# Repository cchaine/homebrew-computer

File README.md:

# Homebrew Computer

Design documents and details about my microprocessorless computer.

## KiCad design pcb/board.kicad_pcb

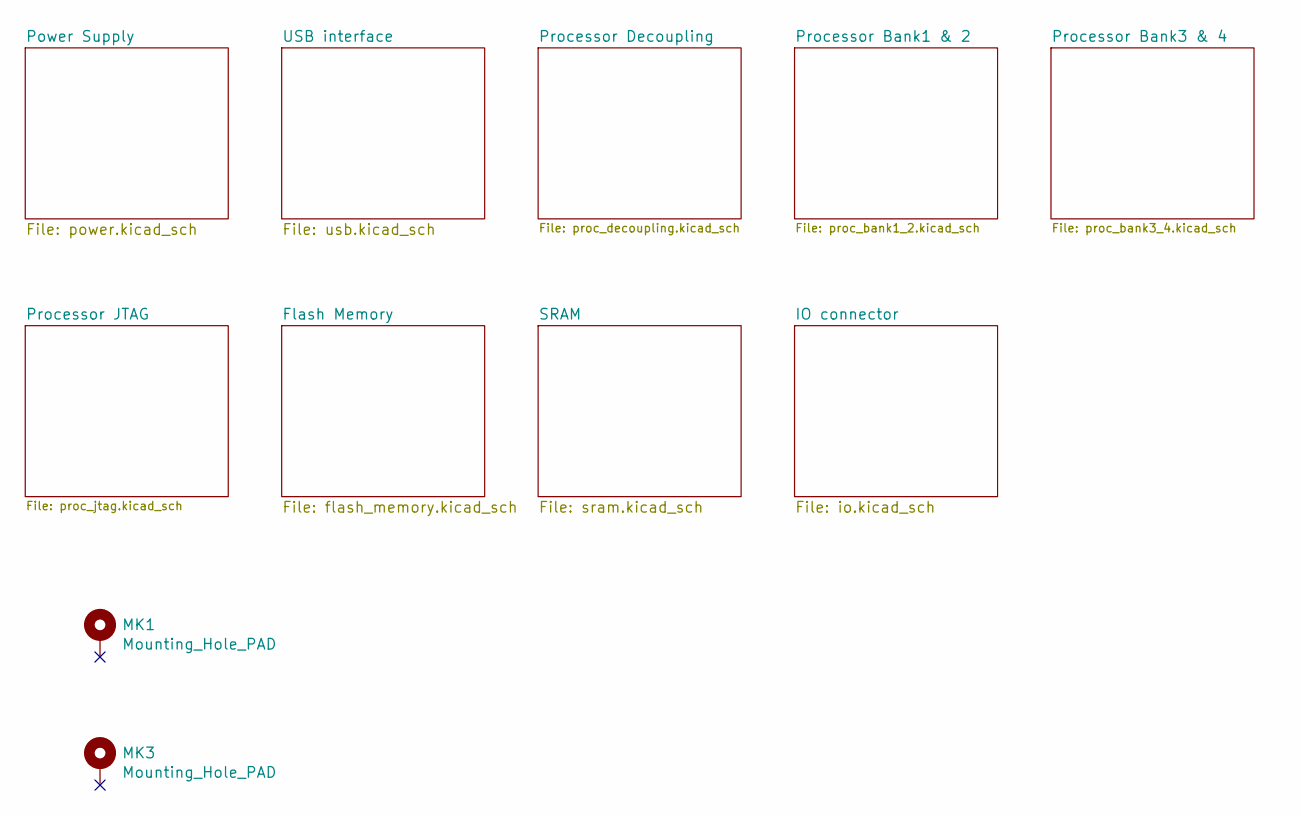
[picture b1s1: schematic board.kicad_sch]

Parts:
MK1, MK3: Mounting_Hole_PAD; MountingHole_2.7mm

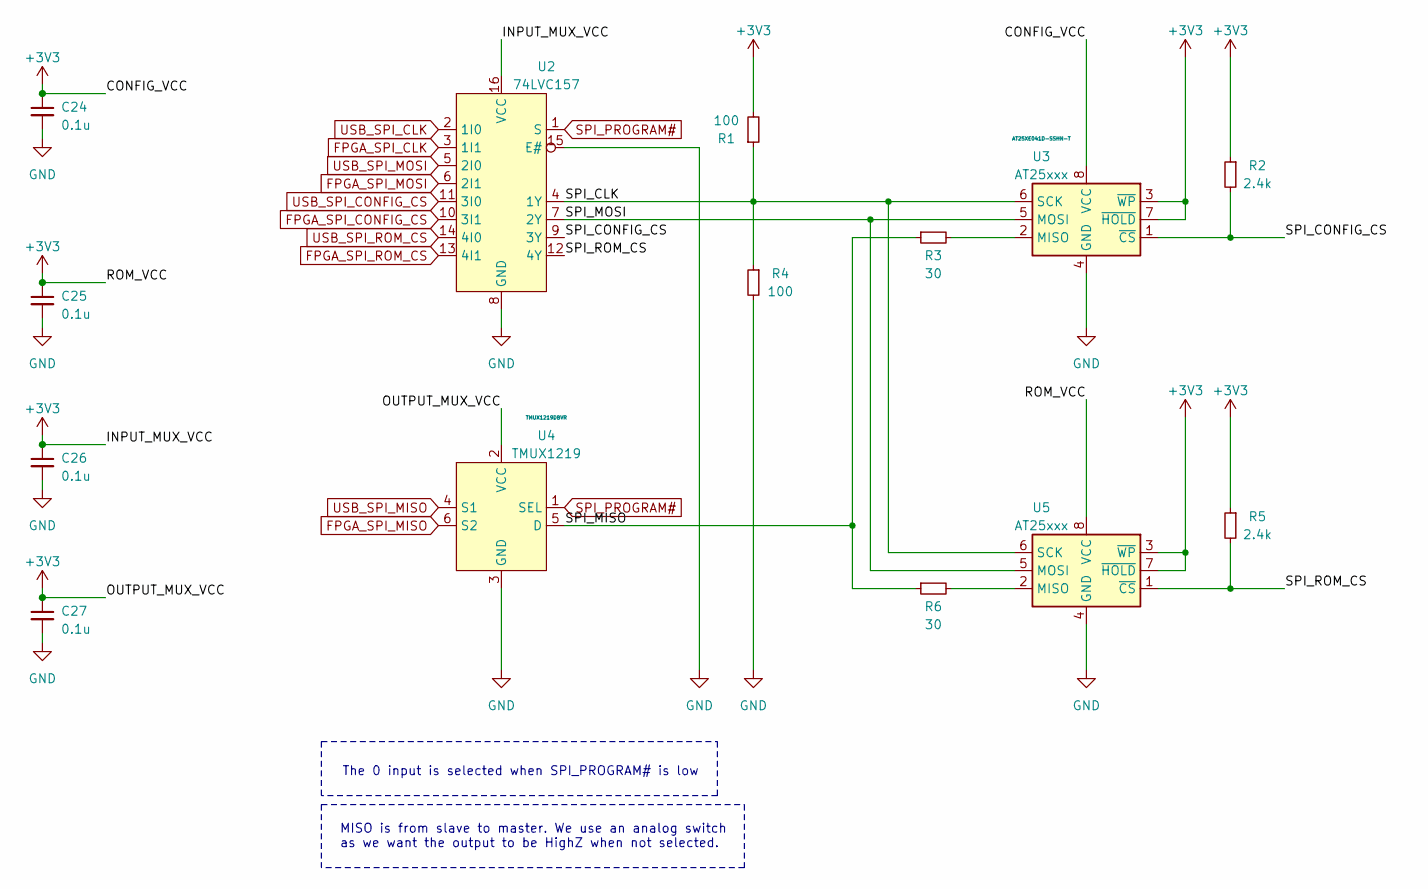
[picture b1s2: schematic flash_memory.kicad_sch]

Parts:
C24, C25, C26, C27: 0.1u; C_0402_1005Metric
R1, R4: 100; R_0402_1005Metric
R2, R5: 2.4k; R_0402_1005Metric
R3, R6: 30; R_0402_1005Metric
U2: 74LVC157; TSSOP-16_4.4x5mm_P0.65mm
U3, U5: AT25xxx; SOIC-8_3.9x4.9mm_P1.27mm
U4: TMUX1219; SOT-23-6

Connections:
/Flash Memory/SPI_CLK: R1.1, R4.1, U2.4 (1Y), U3.6 (SCK), U5.6 (SCK)
/Flash Memory/SPI_CONFIG_CS: R2.2, U2.9 (3Y), U3.1 (~CS)
/Flash Memory/SPI_MISO: R3.1, R6.1, U4.5 (D)
/Flash Memory/SPI_MOSI: U2.7 (2Y), U3.5 (MOSI), U5.5 (MOSI)
/Flash Memory/SPI_ROM_CS: R5.2, U2.12 (4Y), U5.1 (~CS)
FPGA_SPI_CLK: U2.3 (1I1); also elsewhere on the board
FPGA_SPI_CONFIG_CS: U2.10 (3I1); also elsewhere on the board
FPGA_SPI_MISO: U4.6 (S2); also elsewhere on the board
FPGA_SPI_MOSI: U2.6 (2I1); also elsewhere on the board
FPGA_SPI_ROM_CS: U2.13 (4I1); also elsewhere on the board
GND: C24.2, C25.2, C26.2, C27.2, R4.2, U2.8 (GND), U2.15 (E#), U3.4 (GND), U4.3 (GND), U5.4 (GND); also elsewhere on the board
unnamed: R3.2, U3.2 (MISO)
unnamed: R6.2, U5.2 (MISO)
SPI_PROGRAM#: U2.1 (S), U4.1 (SEL); also elsewhere on the board
USB_SPI_CLK: U2.2 (1I0); also elsewhere on the board
USB_SPI_CONFIG_CS: U2.11 (3I0); also elsewhere on the board
USB_SPI_MISO: U4.4 (S1); also elsewhere on the board
USB_SPI_MOSI: U2.5 (2I0); also elsewhere on the board
USB_SPI_ROM_CS: U2.14 (4I0); also elsewhere on the board
VCCAUX: C24.1, C25.1, C26.1, C27.1, R1.2, R2.1, R5.1, U2.16 (VCC), U3.3 (~WP), U3.7 (~HOLD), U3.8 (VCC), U4.2 (VCC), U5.3 (~WP), U5.7 (~HOLD), U5.8 (VCC); also elsewhere on the board

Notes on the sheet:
MISO is from slave to master. We use an analog switch as we want the output to be HighZ when not selected.
The 0 input is selected when SPI_PROGRAM# is low

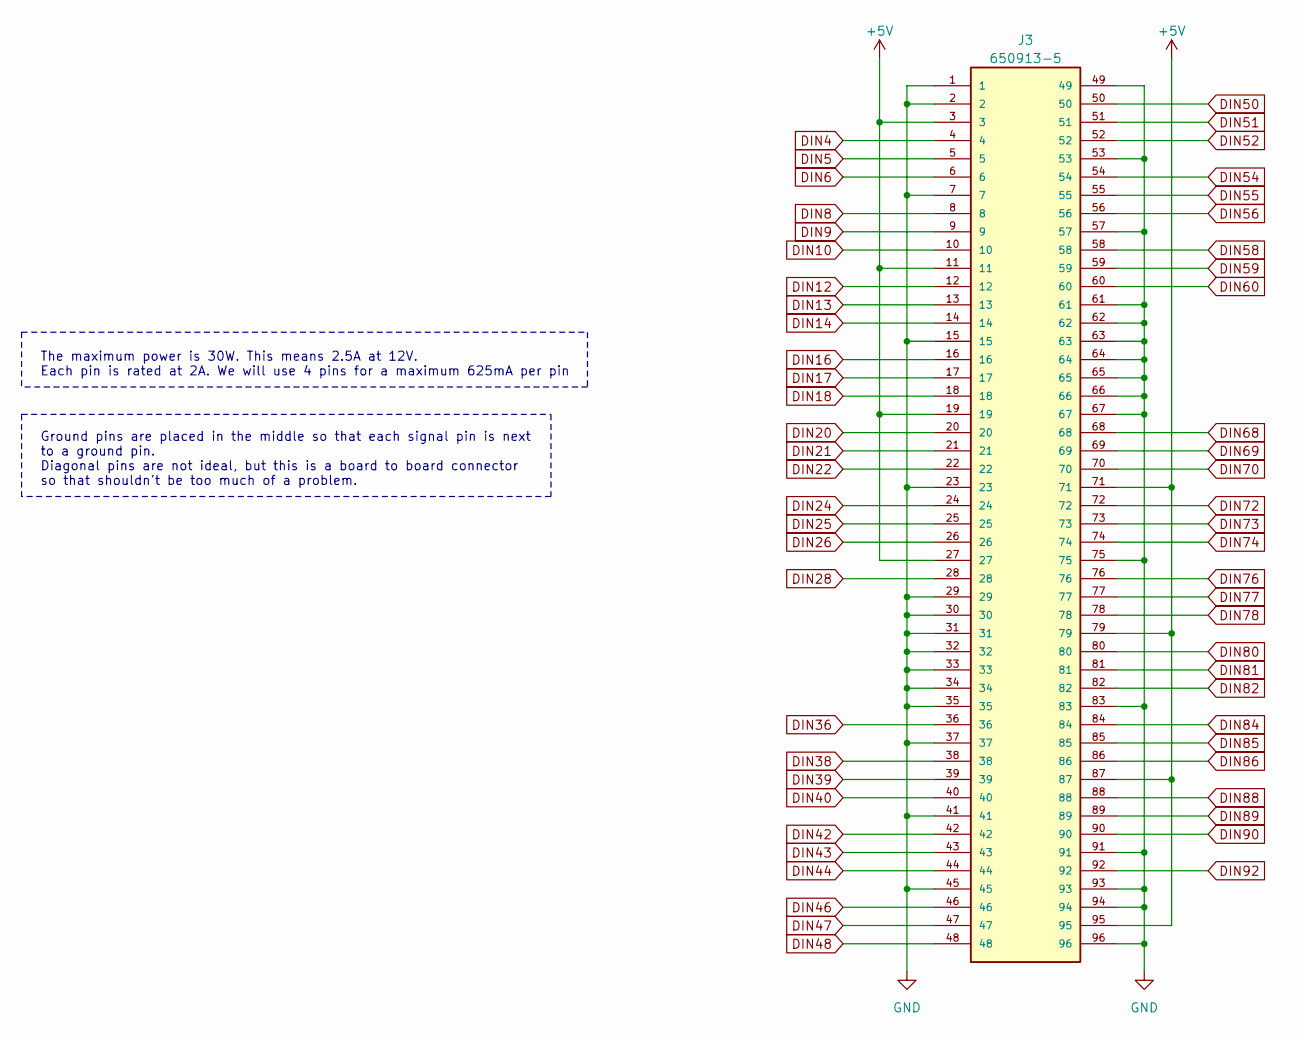
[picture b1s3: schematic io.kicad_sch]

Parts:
J3: 650913-5; TE_650913-5

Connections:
+5V: J3.3, J3.11, J3.19, J3.27, J3.71, J3.79, J3.87, J3.95; also elsewhere on the board
DIN4: J3.4; also elsewhere on the board
DIN5: J3.5; also elsewhere on the board
DIN6: J3.6; also elsewhere on the board
DIN8: J3.8; also elsewhere on the board
DIN9: J3.9; also elsewhere on the board
DIN10: J3.10; also elsewhere on the board
DIN12: J3.12; also elsewhere on the board
DIN13: J3.13; also elsewhere on the board
DIN14: J3.14; also elsewhere on the board
DIN16: J3.16; also elsewhere on the board
DIN17: J3.17; also elsewhere on the board
DIN18: J3.18; also elsewhere on the board
DIN20: J3.20; also elsewhere on the board
DIN21: J3.21; also elsewhere on the board
DIN22: J3.22; also elsewhere on the board
DIN24: J3.24; also elsewhere on the board
DIN25: J3.25; also elsewhere on the board
DIN26: J3.26; also elsewhere on the board
DIN28: J3.28; also elsewhere on the board
DIN36: J3.36; also elsewhere on the board
DIN38: J3.38; also elsewhere on the board
DIN39: J3.39; also elsewhere on the board
DIN40: J3.40; also elsewhere on the board
DIN42: J3.42; also elsewhere on the board
DIN43: J3.43; also elsewhere on the board
DIN44: J3.44; also elsewhere on the board
DIN46: J3.46; also elsewhere on the board
DIN47: J3.47; also elsewhere on the board
DIN48: J3.48; also elsewhere on the board
DIN50: J3.50; also elsewhere on the board
DIN51: J3.51; also elsewhere on the board
DIN52: J3.52; also elsewhere on the board
DIN54: J3.54; also elsewhere on the board
DIN55: J3.55; also elsewhere on the board
DIN56: J3.56; also elsewhere on the board
DIN58: J3.58; also elsewhere on the board
DIN59: J3.59; also elsewhere on the board
DIN60: J3.60; also elsewhere on the board
DIN68: J3.68; also elsewhere on the board
DIN69: J3.69; also elsewhere on the board
DIN70: J3.70; also elsewhere on the board
DIN72: J3.72; also elsewhere on the board
DIN73: J3.73; also elsewhere on the board
DIN74: J3.74; also elsewhere on the board
DIN76: J3.76; also elsewhere on the board
DIN77: J3.77; also elsewhere on the board
DIN78: J3.78; also elsewhere on the board
DIN80: J3.80; also elsewhere on the board
DIN81: J3.81; also elsewhere on the board
DIN82: J3.82; also elsewhere on the board
DIN84: J3.84; also elsewhere on the board
DIN85: J3.85; also elsewhere on the board
DIN86: J3.86; also elsewhere on the board
DIN88: J3.88; also elsewhere on the board
DIN89: J3.89; also elsewhere on the board
DIN90: J3.90; also elsewhere on the board
DIN92: J3.92; also elsewhere on the board
GND: J3.1, J3.2, J3.7, J3.15, J3.23, J3.29, J3.30, J3.31, J3.32, J3.33, J3.34, J3.35, J3.37, J3.41, J3.45, J3.49, J3.53, J3.57, J3.61, J3.62, J3.63, J3.64, J3.65, J3.66, J3.67, J3.75, J3.83, J3.91, J3.93, J3.94, J3.96; also elsewhere on the board

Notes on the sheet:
The maximum power is 30W. This means 2.5A at 12V. Each pin is rated at 2A. We will use 4 pins for a maximum 625mA per pin
Ground pins are placed in the middle so that each signal pin is next to a ground pin. Diagonal pins are not ideal, but this is a board to board connector so that shouldn't be too much of a problem.

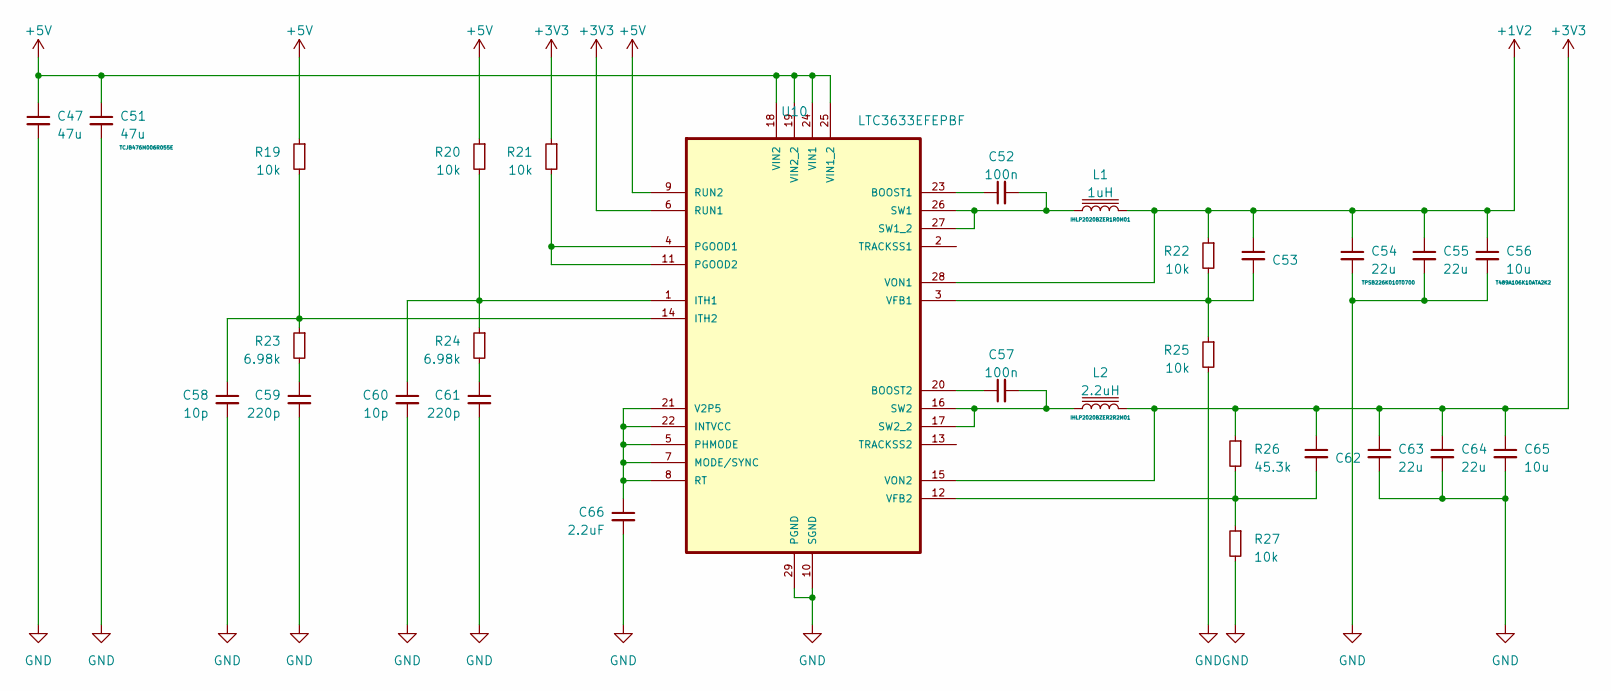
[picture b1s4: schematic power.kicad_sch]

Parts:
C47, C51: 47u; C_1210_3225Metric
C52, C57: 100n; C_0402_1005Metric
C53, C62: NL; C_0603_1608Metric
C54, C55, C63, C64: 22u; C_1206_3216Metric
C56, C65: 10u; C_1206_3216Metric
C58, C60: 10p; C_0402_1005Metric
C59, C61: 220p; C_0402_1005Metric
C66: 2.2uF; C_0603_1608Metric
L1: 1uH; IND_#A915BY-100M=P3
L2: 2.2uH; IND_#A915BY-100M=P3
R19, R20, R21, R22, R25, R27: 10k; R_0402_1005Metric
R23, R24: 6.98k; R_0402_1005Metric
R26: 45.3k; R_0402_1005Metric
U10: LTC3633EFEPBF; SOP65P640X120-29N

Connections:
+5V: C47.1, C51.1, R19.1, R20.1, U10.9 (RUN2), U10.18 (VIN2), U10.19 (VIN2_2), U10.24 (VIN1), U10.25 (VIN1_2); also elsewhere on the board
GND: C47.2, C51.2, C54.2, C55.2, C56.2, C58.2, C59.2, C60.2, C61.2, C63.2, C64.2, C65.2, C66.2, R25.2, R27.2, U10.10 (SGND), U10.29 (PGND); also elsewhere on the board
unnamed: C52.1, U10.23 (BOOST1)
unnamed: C52.2, L1.1, U10.26 (SW1), U10.27 (SW1_2)
unnamed: C53.2, R22.2, R25.1, U10.3 (VFB1)
unnamed: C57.1, U10.20 (BOOST2)
unnamed: C57.2, L2.1, U10.16 (SW2), U10.17 (SW2_2)
unnamed: C58.1, R19.2, R23.1, U10.14 (ITH2)
unnamed: C59.1, R23.2
unnamed: C60.1, R20.2, R24.1, U10.1 (ITH1)
unnamed: C61.1, R24.2
unnamed: C62.2, R26.2, R27.1, U10.12 (VFB2)
unnamed: C66.1, U10.5 (PHMODE), U10.7 (MODE/SYNC), U10.8 (RT), U10.21 (V2P5), U10.22 (INTVCC)
unnamed: R21.2, U10.4 (PGOOD1), U10.11 (PGOOD2)
VCCAUX: C62.1, C63.1, C64.1, C65.1, L2.2, R21.1, R26.1, U10.6 (RUN1), U10.15 (VON2); also elsewhere on the board
VCCINT: C53.1, C54.1, C55.1, C56.1, L1.2, R22.1, U10.28 (VON1); also elsewhere on the board

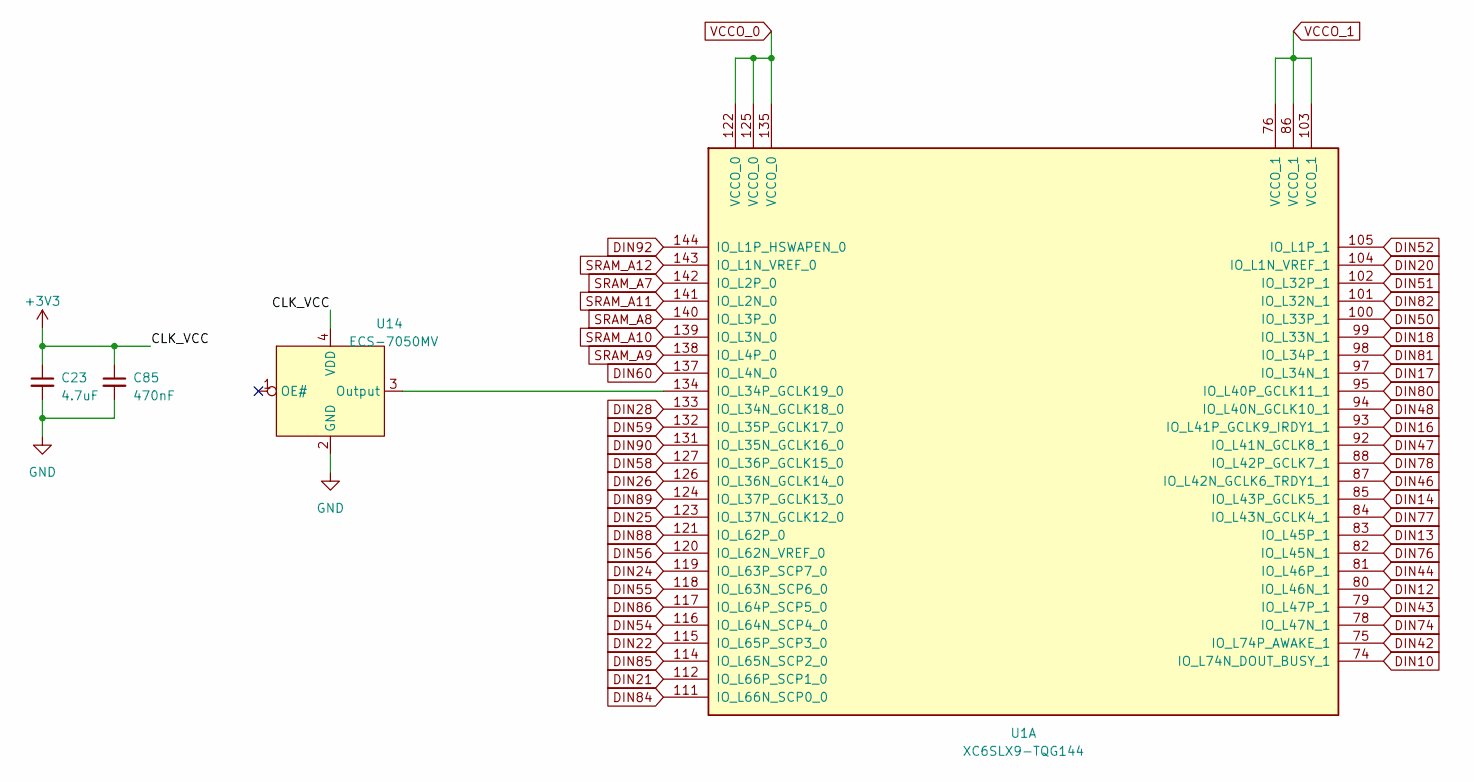
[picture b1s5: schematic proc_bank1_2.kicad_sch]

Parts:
C23: 4.7uF; C_0805_2012Metric
C85: 470nF; C_0402_1005Metric
U1: XC6SLX9-TQG144; TQFP-144_20x20mm_P0.5mm
U14: ECS-7050MV

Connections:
DIN10: U1.74 (IO_L74N_DOUT_BUSY_1); also elsewhere on the board
DIN12: U1.80 (IO_L46N_1); also elsewhere on the board
DIN13: U1.83 (IO_L45P_1); also elsewhere on the board
DIN14: U1.85 (IO_L43P_GCLK5_1); also elsewhere on the board
DIN16: U1.93 (IO_L41P_GCLK9_IRDY1_1); also elsewhere on the board
DIN17: U1.97 (IO_L34N_1); also elsewhere on the board
DIN18: U1.99 (IO_L33N_1); also elsewhere on the board
DIN20: U1.104 (IO_L1N_VREF_1); also elsewhere on the board
DIN21: U1.112 (IO_L66P_SCP1_0); also elsewhere on the board
DIN22: U1.115 (IO_L65P_SCP3_0); also elsewhere on the board
DIN24: U1.119 (IO_L63P_SCP7_0); also elsewhere on the board
DIN25: U1.123 (IO_L37N_GCLK12_0); also elsewhere on the board
DIN26: U1.126 (IO_L36N_GCLK14_0); also elsewhere on the board
DIN28: U1.133 (IO_L34N_GCLK18_0); also elsewhere on the board
DIN42: U1.75 (IO_L74P_AWAKE_1); also elsewhere on the board
DIN43: U1.79 (IO_L47P_1); also elsewhere on the board
DIN44: U1.81 (IO_L46P_1); also elsewhere on the board
DIN46: U1.87 (IO_L42N_GCLK6_TRDY1_1); also elsewhere on the board
DIN47: U1.92 (IO_L41N_GCLK8_1); also elsewhere on the board
DIN48: U1.94 (IO_L40N_GCLK10_1); also elsewhere on the board
DIN50: U1.100 (IO_L33P_1); also elsewhere on the board
DIN51: U1.102 (IO_L32P_1); also elsewhere on the board
DIN52: U1.105 (IO_L1P_1); also elsewhere on the board
DIN54: U1.116 (IO_L64N_SCP4_0); also elsewhere on the board
DIN55: U1.118 (IO_L63N_SCP6_0); also elsewhere on the board
DIN56: U1.120 (IO_L62N_VREF_0); also elsewhere on the board
DIN58: U1.127 (IO_L36P_GCLK15_0); also elsewhere on the board
DIN59: U1.132 (IO_L35P_GCLK17_0); also elsewhere on the board
DIN60: U1.137 (IO_L4N_0); also elsewhere on the board
DIN74: U1.78 (IO_L47N_1); also elsewhere on the board
DIN76: U1.82 (IO_L45N_1); also elsewhere on the board
DIN77: U1.84 (IO_L43N_GCLK4_1); also elsewhere on the board
DIN78: U1.88 (IO_L42P_GCLK7_1); also elsewhere on the board
DIN80: U1.95 (IO_L40P_GCLK11_1); also elsewhere on the board
DIN81: U1.98 (IO_L34P_1); also elsewhere on the board
DIN82: U1.101 (IO_L32N_1); also elsewhere on the board
DIN84: U1.111 (IO_L66N_SCP0_0); also elsewhere on the board
DIN85: U1.114 (IO_L65N_SCP2_0); also elsewhere on the board
DIN86: U1.117 (IO_L64P_SCP5_0); also elsewhere on the board
DIN88: U1.121 (IO_L62P_0); also elsewhere on the board
DIN89: U1.124 (IO_L37P_GCLK13_0); also elsewhere on the board
DIN90: U1.131 (IO_L35N_GCLK16_0); also elsewhere on the board
DIN92: U1.144 (IO_L1P_HSWAPEN_0); also elsewhere on the board
GND: C23.2, C85.2, U14.2 (GND); also elsewhere on the board
unnamed: U1.134 (IO_L34P_GCLK19_0), U14.3 (Output)
SRAM_A7: U1.142 (IO_L2P_0); also elsewhere on the board
SRAM_A8: U1.140 (IO_L3P_0); also elsewhere on the board
SRAM_A9: U1.138 (IO_L4P_0); also elsewhere on the board
SRAM_A10: U1.139 (IO_L3N_0); also elsewhere on the board
SRAM_A11: U1.141 (IO_L2N_0); also elsewhere on the board
SRAM_A12: U1.143 (IO_L1N_VREF_0); also elsewhere on the board
VCCAUX: C23.1, C85.1, U1.76 (VCCO_1), U1.86 (VCCO_1), U1.103 (VCCO_1), U1.122 (VCCO_0), U1.125 (VCCO_0), U1.135 (VCCO_0), U14.4 (VDD); also elsewhere on the board

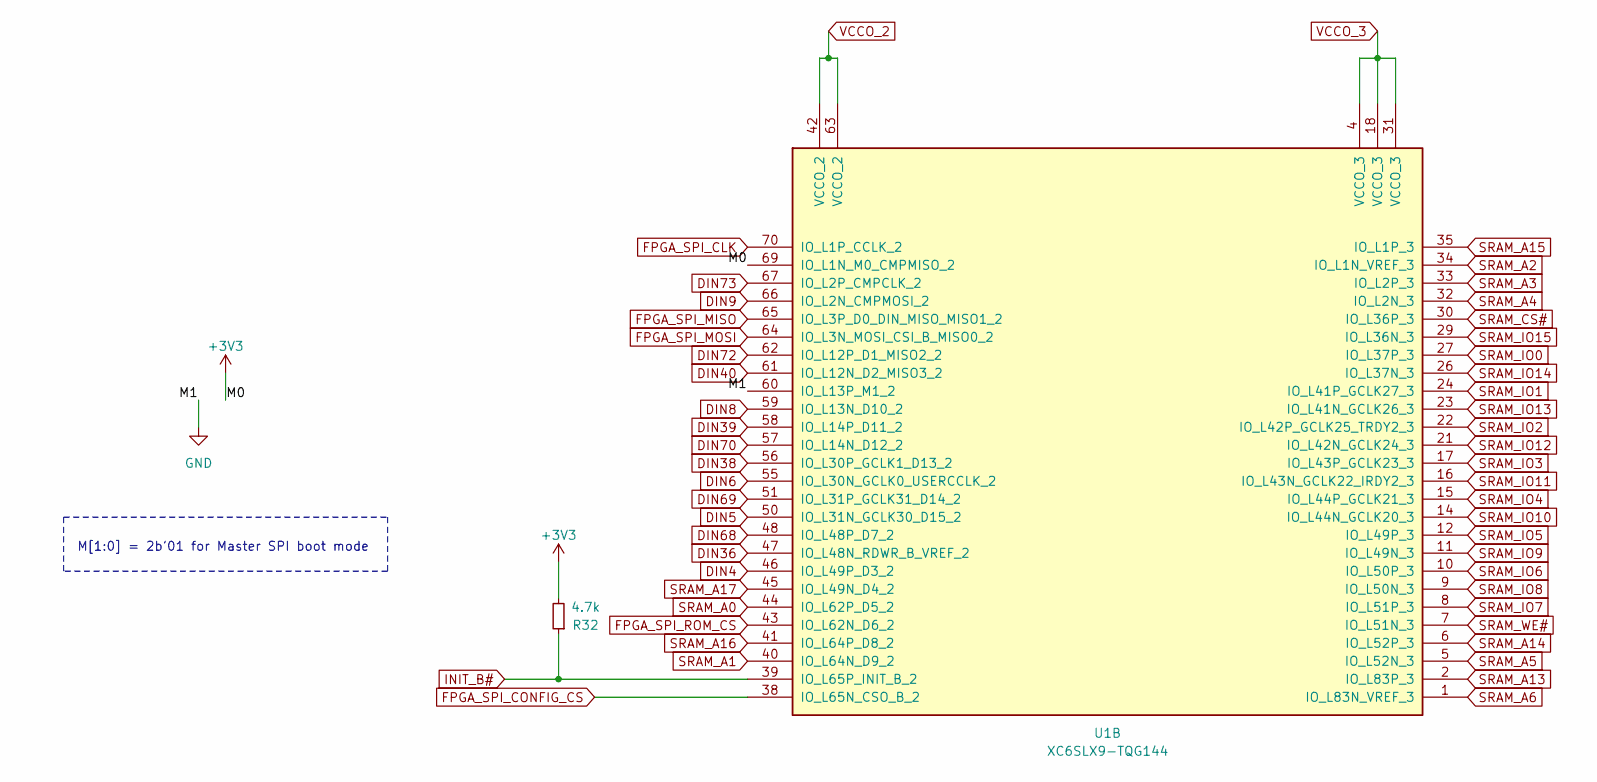
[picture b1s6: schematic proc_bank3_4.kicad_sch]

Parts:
R32: 4.7k; R_0402_1005Metric
U1: XC6SLX9-TQG144; TQFP-144_20x20mm_P0.5mm

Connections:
DIN4: U1.46 (IO_L49P_D3_2); also elsewhere on the board
DIN5: U1.50 (IO_L31N_GCLK30_D15_2); also elsewhere on the board
DIN6: U1.55 (IO_L30N_GCLK0_USERCCLK_2); also elsewhere on the board
DIN8: U1.59 (IO_L13N_D10_2); also elsewhere on the board
DIN9: U1.66 (IO_L2N_CMPMOSI_2); also elsewhere on the board
DIN36: U1.47 (IO_L48N_RDWR_B_VREF_2); also elsewhere on the board
DIN38: U1.56 (IO_L30P_GCLK1_D13_2); also elsewhere on the board
DIN39: U1.58 (IO_L14P_D11_2); also elsewhere on the board
DIN40: U1.61 (IO_L12N_D2_MISO3_2); also elsewhere on the board
DIN68: U1.48 (IO_L48P_D7_2); also elsewhere on the board
DIN69: U1.51 (IO_L31P_GCLK31_D14_2); also elsewhere on the board
DIN70: U1.57 (IO_L14N_D12_2); also elsewhere on the board
DIN72: U1.62 (IO_L12P_D1_MISO2_2); also elsewhere on the board
DIN73: U1.67 (IO_L2P_CMPCLK_2); also elsewhere on the board
FPGA_SPI_CLK: U1.70 (IO_L1P_CCLK_2); also elsewhere on the board
FPGA_SPI_CONFIG_CS: U1.38 (IO_L65N_CSO_B_2); also elsewhere on the board
FPGA_SPI_MISO: U1.65 (IO_L3P_D0_DIN_MISO_MISO1_2); also elsewhere on the board
FPGA_SPI_MOSI: U1.64 (IO_L3N_MOSI_CSI_B_MISO0_2); also elsewhere on the board
FPGA_SPI_ROM_CS: U1.43 (IO_L62N_D6_2); also elsewhere on the board
GND: U1.60 (IO_L13P_M1_2); also elsewhere on the board
INIT_B#: R32.1, U1.39 (IO_L65P_INIT_B_2); also elsewhere on the board
SRAM_A0: U1.44 (IO_L62P_D5_2); also elsewhere on the board
SRAM_A1: U1.40 (IO_L64N_D9_2); also elsewhere on the board
SRAM_A2: U1.34 (IO_L1N_VREF_3); also elsewhere on the board
SRAM_A3: U1.33 (IO_L2P_3); also elsewhere on the board
SRAM_A4: U1.32 (IO_L2N_3); also elsewhere on the board
SRAM_A5: U1.5 (IO_L52N_3); also elsewhere on the board
SRAM_A6: U1.1 (IO_L83N_VREF_3); also elsewhere on the board
SRAM_A13: U1.2 (IO_L83P_3); also elsewhere on the board
SRAM_A14: U1.6 (IO_L52P_3); also elsewhere on the board
SRAM_A15: U1.35 (IO_L1P_3); also elsewhere on the board
SRAM_A16: U1.41 (IO_L64P_D8_2); also elsewhere on the board
SRAM_A17: U1.45 (IO_L49N_D4_2); also elsewhere on the board
SRAM_CS#: U1.30 (IO_L36P_3); also elsewhere on the board
SRAM_IO0: U1.27 (IO_L37P_3); also elsewhere on the board
SRAM_IO1: U1.24 (IO_L41P_GCLK27_3); also elsewhere on the board
SRAM_IO2: U1.22 (IO_L42P_GCLK25_TRDY2_3); also elsewhere on the board
SRAM_IO3: U1.17 (IO_L43P_GCLK23_3); also elsewhere on the board
SRAM_IO4: U1.15 (IO_L44P_GCLK21_3); also elsewhere on the board
SRAM_IO5: U1.12 (IO_L49P_3); also elsewhere on the board
SRAM_IO6: U1.10 (IO_L50P_3); also elsewhere on the board
SRAM_IO7: U1.8 (IO_L51P_3); also elsewhere on the board
SRAM_IO8: U1.9 (IO_L50N_3); also elsewhere on the board
SRAM_IO9: U1.11 (IO_L49N_3); also elsewhere on the board
SRAM_IO10: U1.14 (IO_L44N_GCLK20_3); also elsewhere on the board
SRAM_IO11: U1.16 (IO_L43N_GCLK22_IRDY2_3); also elsewhere on the board
SRAM_IO12: U1.21 (IO_L42N_GCLK24_3); also elsewhere on the board
SRAM_IO13: U1.23 (IO_L41N_GCLK26_3); also elsewhere on the board
SRAM_IO14: U1.26 (IO_L37N_3); also elsewhere on the board
SRAM_IO15: U1.29 (IO_L36N_3); also elsewhere on the board
SRAM_WE#: U1.7 (IO_L51N_3); also elsewhere on the board
VCCAUX: R32.2, U1.4 (VCCO_3), U1.18 (VCCO_3), U1.31 (VCCO_3), U1.42 (VCCO_2), U1.63 (VCCO_2), U1.69 (IO_L1N_M0_CMPMISO_2); also elsewhere on the board

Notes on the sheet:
M[1:0] = 2b'01 for Master SPI boot mode

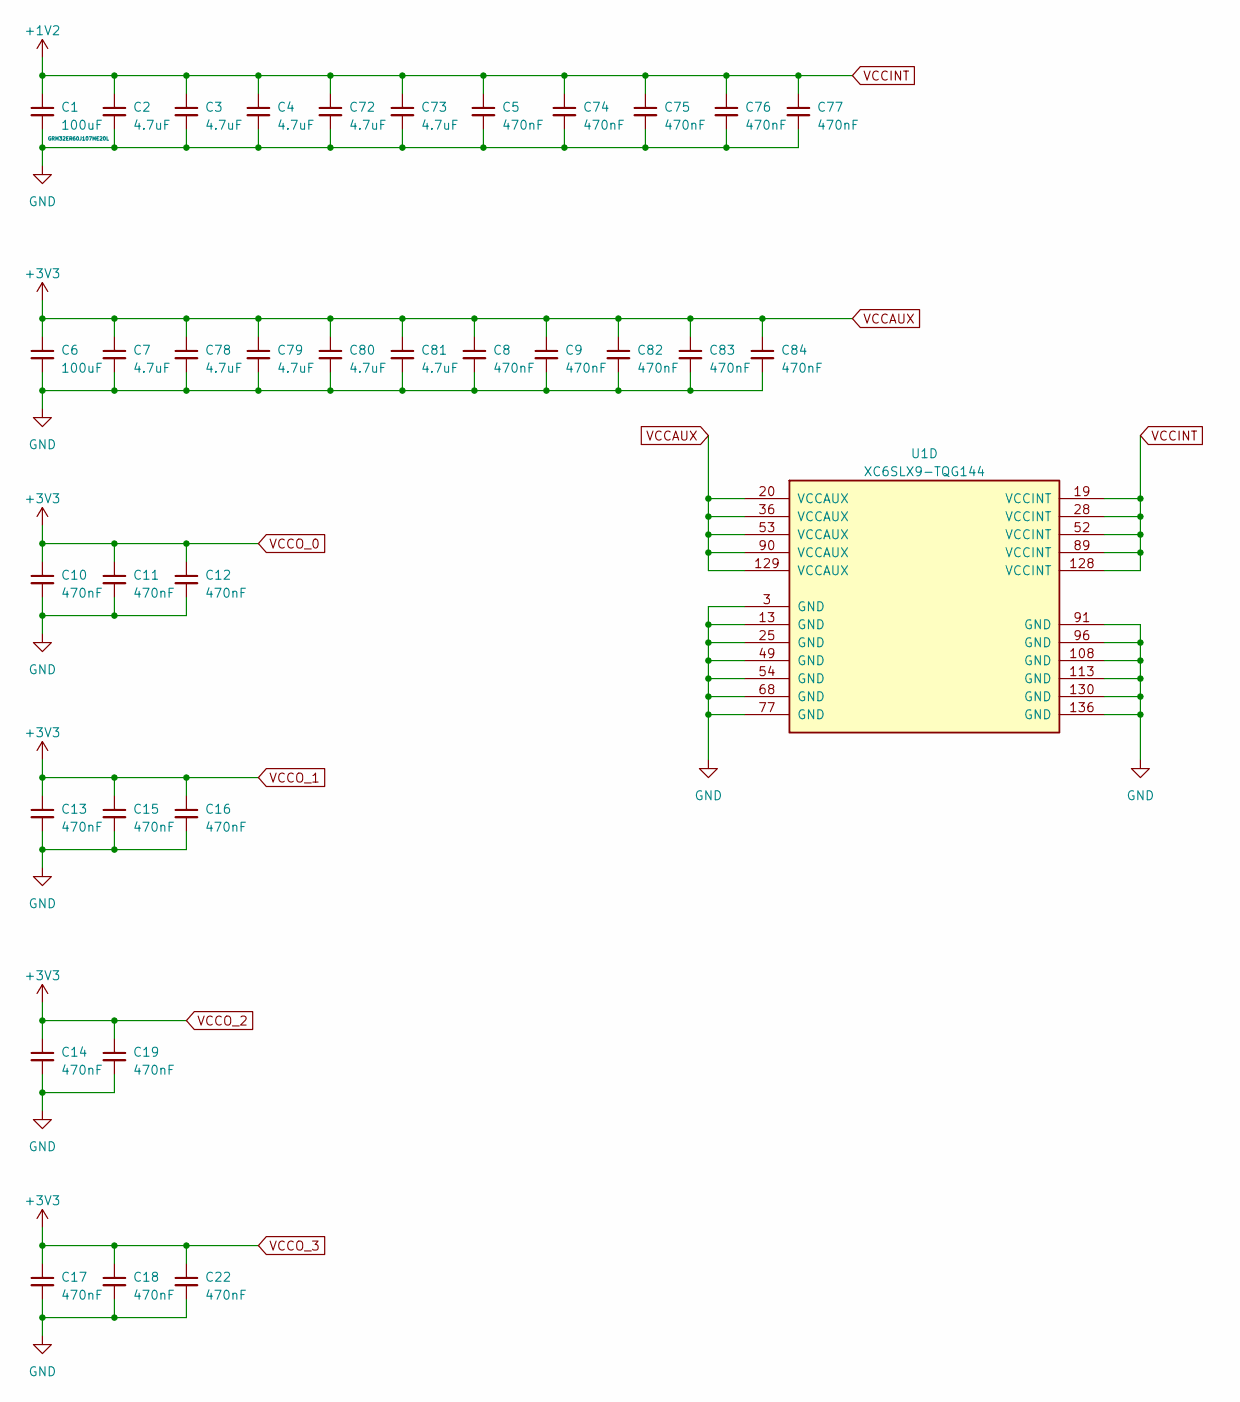
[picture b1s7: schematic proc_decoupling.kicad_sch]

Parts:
C1, C6: 100uF; C_1210_3225Metric
C2, C3, C4, C7, C72, C73, C78, C79, C80, C81: 4.7uF; C_0805_2012Metric
C5, C8, C9, C10, C11, C12, C13, C14, C15, C16, C17, C18, C19, C22, C74, C75, C76, C77, C82, C83, C84: 470nF; C_0402_1005Metric
U1: XC6SLX9-TQG144; TQFP-144_20x20mm_P0.5mm

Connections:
GND: C1.2, C2.2, C3.2, C4.2, C5.2, C6.2, C7.2, C8.2, C9.2, C10.2, C11.2, C12.2, C13.2, C14.2, C15.2, C16.2, C17.2, C18.2, C19.2, C22.2, C72.2, C73.2, C74.2, C75.2, C76.2, C77.2, C78.2, C79.2, C80.2, C81.2, C82.2, C83.2, C84.2, U1.3 (GND), U1.13 (GND), U1.25 (GND), U1.49 (GND), U1.54 (GND), U1.68 (GND), U1.77 (GND), U1.91 (GND), U1.96 (GND), U1.108 (GND), U1.113 (GND), U1.130 (GND), U1.136 (GND); also elsewhere on the board
VCCAUX: C6.1, C7.1, C8.1, C9.1, C10.1, C11.1, C12.1, C13.1, C14.1, C15.1, C16.1, C17.1, C18.1, C19.1, C22.1, C78.1, C79.1, C80.1, C81.1, C82.1, C83.1, C84.1, U1.20 (VCCAUX), U1.36 (VCCAUX), U1.53 (VCCAUX), U1.90 (VCCAUX), U1.129 (VCCAUX); also elsewhere on the board
VCCINT: C1.1, C2.1, C3.1, C4.1, C5.1, C72.1, C73.1, C74.1, C75.1, C76.1, C77.1, U1.19 (VCCINT), U1.28 (VCCINT), U1.52 (VCCINT), U1.89 (VCCINT), U1.128 (VCCINT); also elsewhere on the board

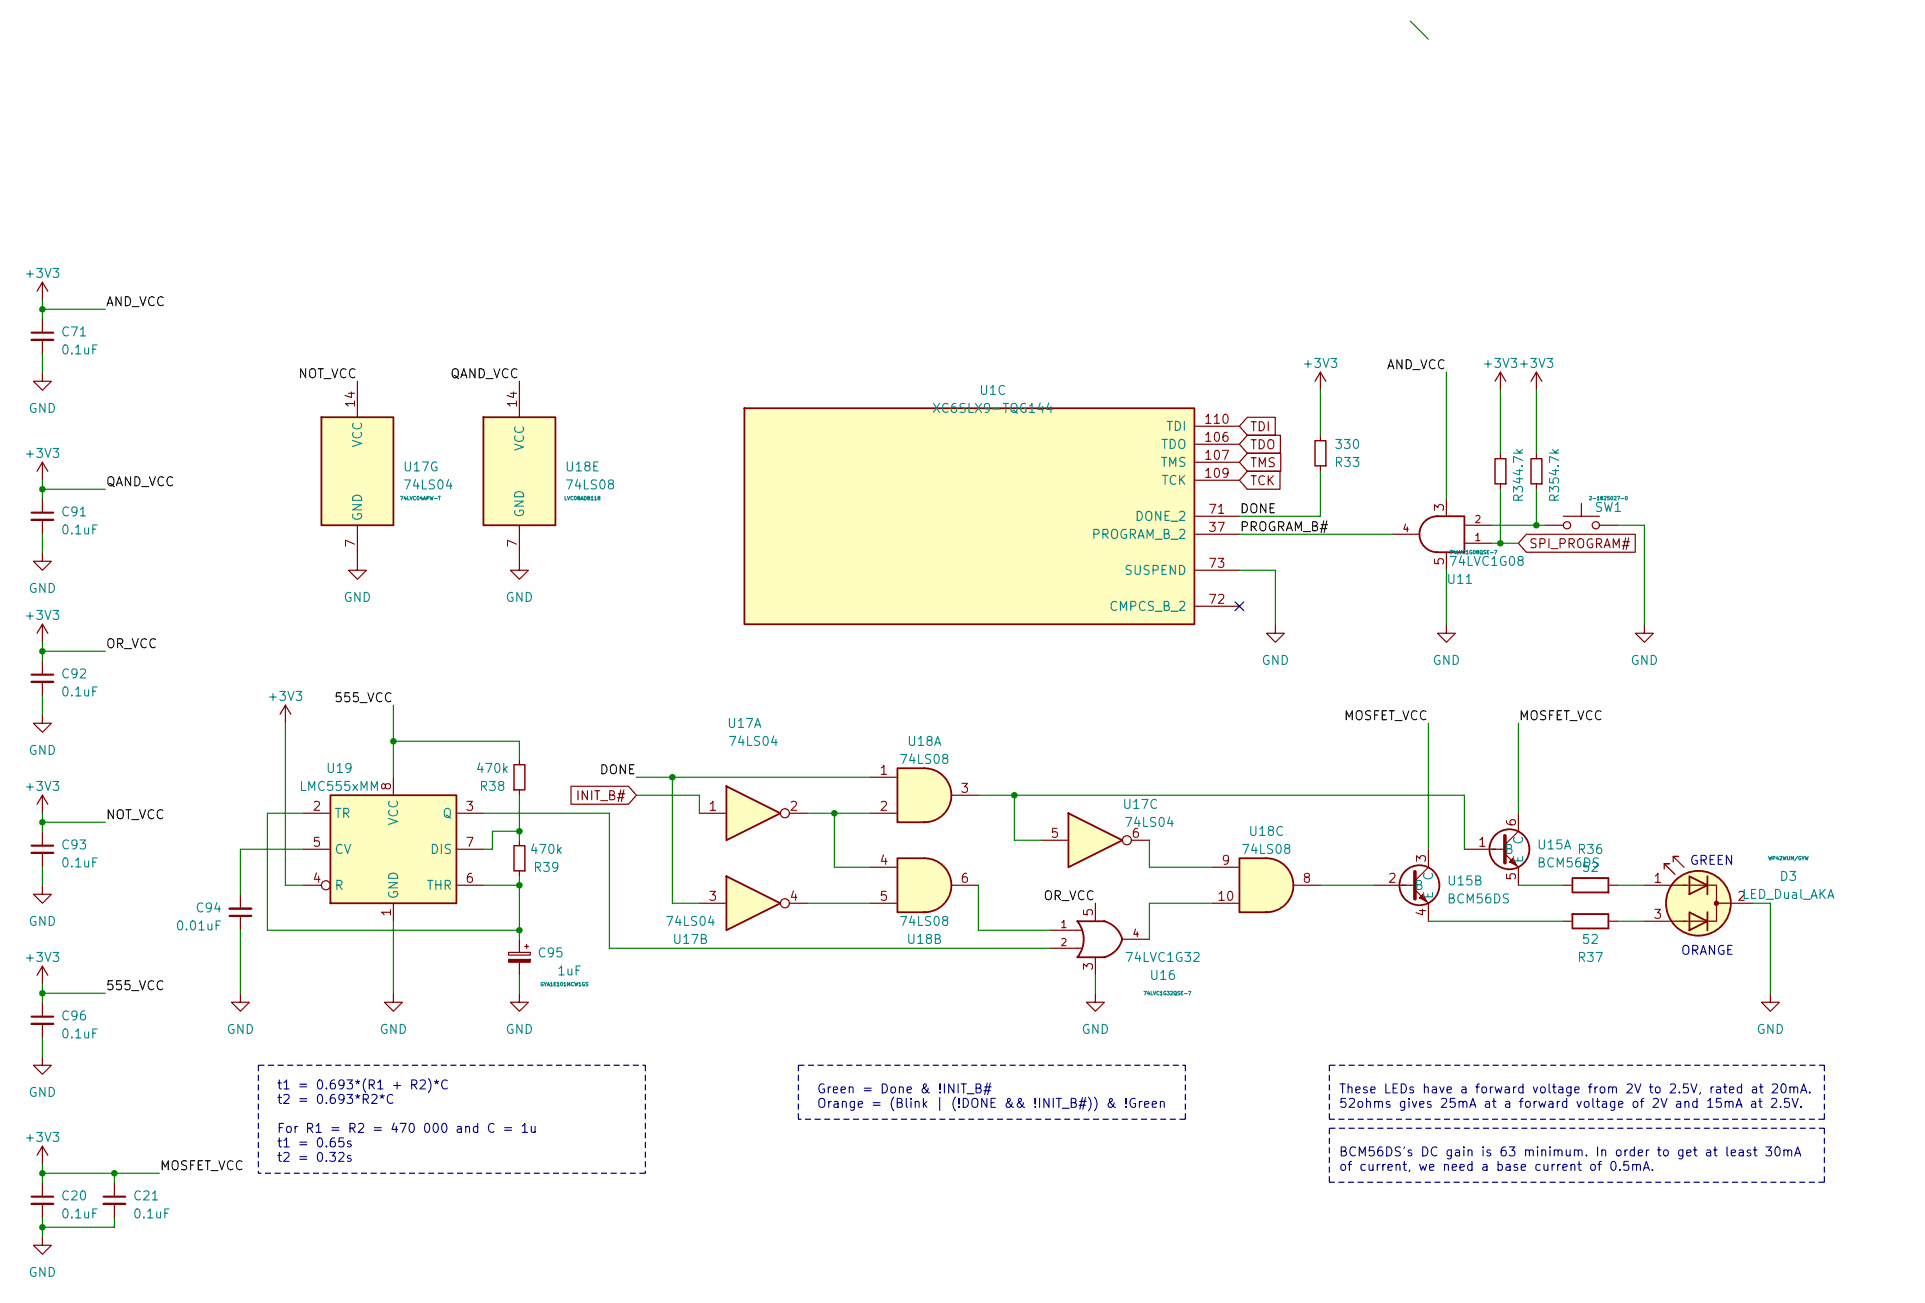
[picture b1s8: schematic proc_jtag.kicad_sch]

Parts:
C20, C21, C71, C91, C92, C93, C96: 0.1uF; C_0402_1005Metric
C94: 0.01uF; C_0402_1005Metric
C95: 1uF; CP_Elec_6.3x7.7
D3: LED_Dual_AKA; WP42WUM,GYW
R33: 330; R_0402_1005Metric
R34, R35: 4.7k; R_0402_1005Metric
R36, R37: 52; R_0402_1005Metric
R38, R39: 470k; R_0402_1005Metric
SW1: SW_Push; 2-1825027-0
U1: XC6SLX9-TQG144; TQFP-144_20x20mm_P0.5mm
U11: 74LVC1G08; SOT-353_SC-70-5
U15: BCM56DS; TSOP-6_1.65x3.05mm_P0.95mm
U16: 74LVC1G32; SOT-353_SC-70-5
U17: 74LS04; TSSOP-14_4.4x5mm_P0.65mm
U18: 74LS08; SSOP-14_5.3x6.2mm_P0.65mm
U19: LMC555xMM; VSSOP-8_3.0x3.0mm_P0.65mm

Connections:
/Processor JTAG/DONE: R33.1, U1.71 (DONE_2), U17.3, U18.1
/Processor JTAG/PROGRAM_B#: U1.37 (PROGRAM_B_2), U11.4
GND: C20.2, C21.2, C71.2, C91.2, C92.2, C93.2, C94.1, C95.2, C96.2, D3.2 (K), SW1.2, U1.73 (SUSPEND), U11.5, U16.3, U17.7 (GND), U18.7 (GND), U19.1 (GND); also elsewhere on the board
INIT_B#: U17.1; also elsewhere on the board
unnamed: C94.2, U19.5 (CV)
unnamed: C95.1, R39.1, U19.2 (TR), U19.6 (THR)
unnamed: D3.1 (A1), R36.2
unnamed: D3.3 (A2), R37.1
unnamed: R35.1, SW1.1, U11.2
unnamed: R36.1, U15.5 (E)
unnamed: R37.2, U15.4 (E)
unnamed: R38.1, R39.2, U19.7 (DIS)
unnamed: U15.1 (B), U17.5, U18.3
unnamed: U15.2 (B), U18.8
unnamed: U16.1, U18.6
unnamed: U16.2, U19.3 (Q)
unnamed: U16.4, U18.10
unnamed: U17.2, U18.2, U18.4
unnamed: U17.4, U18.5
unnamed: U17.6, U18.9
SPI_PROGRAM#: R34.1, U11.1; also elsewhere on the board
TCK: U1.109 (TCK); also elsewhere on the board
TDI: U1.110 (TDI); also elsewhere on the board
TDO: U1.106 (TDO); also elsewhere on the board
TMS: U1.107 (TMS); also elsewhere on the board
VCCAUX: C20.1, C21.1, C71.1, C91.1, C92.1, C93.1, C96.1, R33.2, R34.2, R35.2, R38.2, U11.3, U15.3 (C), U15.6 (C), U16.5, U17.14 (VCC), U18.14 (VCC), U19.4 (R), U19.8 (VCC); also elsewhere on the board

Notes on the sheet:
t1 = 0.693*(R1 + R2)*C t2 = 0.693*R2*C For R1 = R2 = 470 000 and C = 1u t1 = 0.65s t2 = 0.32s
Green = Done & !INIT_B# Orange = (Blink | (!DONE && !INIT_B#)) & !Green
These LEDs have a forward voltage from 2V to 2.5V, rated at 20mA. 52ohms gives 25mA at a forward voltage of 2V and 15mA at 2.5V.
BCM56DS's DC gain is 63 minimum. In order to get at least 30mA of current, we need a base current of 0.5mA.
ORANGE
GREEN

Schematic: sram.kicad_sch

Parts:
C67, C70: 4.7u; CP_Elec_4x4.5
C68, C69: 0.1u; C_0402_1005Metric
U12: IS61WV25616EFBLL; TSOP-II-44_10.16x18.41mm_P0.8mm

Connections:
GND: C67.2, C68.2, C69.2, C70.2, U12.12 (VSS), U12.34 (VSS), U12.39 (LB#), U12.40 (UB#), U12.41 (OE#); also elsewhere on the board
SRAM_A0: U12.1 (A0); also elsewhere on the board
SRAM_A1: U12.2 (A1); also elsewhere on the board
SRAM_A2: U12.3 (A2); also elsewhere on the board
SRAM_A3: U12.4 (A3); also elsewhere on the board
SRAM_A4: U12.5 (A4); also elsewhere on the board
SRAM_A5: U12.18 (A5); also elsewhere on the board
SRAM_A6: U12.19 (A6); also elsewhere on the board
SRAM_A7: U12.20 (A7); also elsewhere on the board
SRAM_A8: U12.21 (A8); also elsewhere on the board
SRAM_A9: U12.22 (A9); also elsewhere on the board
SRAM_A10: U12.23 (A10); also elsewhere on the board
SRAM_A11: U12.24 (A11); also elsewhere on the board
SRAM_A12: U12.25 (A12); also elsewhere on the board
SRAM_A13: U12.26 (A13); also elsewhere on the board
SRAM_A14: U12.27 (A14); also elsewhere on the board
SRAM_A15: U12.42 (A15); also elsewhere on the board
SRAM_A16: U12.43 (A16); also elsewhere on the board
SRAM_A17: U12.44 (A17); also elsewhere on the board
SRAM_CS#: U12.6 (CS#); also elsewhere on the board
SRAM_IO0: U12.7 (IO0); also elsewhere on the board
SRAM_IO1: U12.8 (IO1); also elsewhere on the board
SRAM_IO2: U12.9 (IO2); also elsewhere on the board
SRAM_IO3: U12.10 (IO3); also elsewhere on the board
SRAM_IO4: U12.13 (IO4); also elsewhere on the board
SRAM_IO5: U12.14 (IO5); also elsewhere on the board
SRAM_IO6: U12.15 (IO6); also elsewhere on the board
SRAM_IO7: U12.16 (IO7); also elsewhere on the board
SRAM_IO8: U12.29 (IO8); also elsewhere on the board
SRAM_IO9: U12.30 (IO9); also elsewhere on the board
SRAM_IO10: U12.31 (IO10); also elsewhere on the board
SRAM_IO11: U12.32 (IO11); also elsewhere on the board
SRAM_IO12: U12.35 (IO12); also elsewhere on the board
SRAM_IO13: U12.36 (IO13); also elsewhere on the board
SRAM_IO14: U12.37 (IO14); also elsewhere on the board
SRAM_IO15: U12.38 (IO15); also elsewhere on the board
SRAM_WE#: U12.17 (WE#); also elsewhere on the board
VCCAUX: C67.1, C68.1, C69.1, C70.1, U12.11 (VDD), U12.33 (VDD); also elsewhere on the board
